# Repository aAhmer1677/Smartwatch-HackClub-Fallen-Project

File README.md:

# Smartwatch // HackClub Fallen Project

An open-source smartwatch built from scratch for the Hack Club Fallen. It runs on bare-metal ESP32-S3 with [[additional functions to be added]]

## The Backstory
Smartwatches have potential: You can strap them to your wrist and wear them everywhere. 

This smartwatch could:
- **Launch a private gateway:** you and your friends can then play in class.
- **Allow WIFI Connection to Your Mobile:** useful for that day you forgot your phone (basically calling with no additional sim card).
- **and much more**

I wanted to build a project so that other devs around the world can build upon this watch, including cool and interesting features that I couldn't have come up with myself.

## Compilation & Development

### We will be using:
- **ESP-IDF** - to compile and flash the firmware to the ESP32-S3
- **Android Studio** - to build and flash the Smartwatch App to our Android device *Samsung Galaxy A37 5G in my case*
- **EEZ Studio** - to create and compile the UI in LVGL
- **VS Code** - as the IDE for our overall project

### 1. Flash the firmware to the custom PCB

**Set the target device as an ESP32-S3**
```powershell
idf.py set-target esp32s3
```

**Open the built in terminal menu to configure variables**
```powershell
idf.py menuconfig
```

**Firmware Compilation**
```powershell
idf.py build
```

**Firmware Flashing & Serial Monitoring**
```powershell
# Replace COM3 with your own port
idf.py -p COM3 flash monitor
```

## File Structure
[To be finalised]

```text
Smartwatch Project
├── .github/
├── 3d-models/
|   ├── Chasis/
|   ├── Desings/
|   ├── Strap/
|   └── to print/
├── Android App/
├── assets/
|   ├── plan/
|   └── README/
├── PCB and Schematics/
├── firmware/
|   ├── managed-components/
|   ├── ui/
|   ├── CMakeLists.txt
|   ├── idf_component.yml
|   └── sdkconfig
├── .env.example
├── .gitignore
├── BOM.csv
├── LICENSE
├── plan.md
└── README.md
```

---
## The Project Plan
[`plan.md`](plan.md)

## Images of Product
### 3D Designs

## To Print
- ☐ Smartwatch chasis backplate
- ☐ Smartwatch chasis body
- ☐ Smartwatch strap long black + white mold
- ☐ Smartwatch strap long black mold
- ☐ Smartwatch strap short black + white mold
- ☐ Smartwatch strap short black mold
- ☐ Smartwatch strap short pin
- ☑

---

Built by Abdullah Ahmer for **Hack Club Fallen**

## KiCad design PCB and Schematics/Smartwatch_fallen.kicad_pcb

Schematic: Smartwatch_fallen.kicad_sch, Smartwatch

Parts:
C1, C2, C3, C4, C5, C6, C8, C12, C17, C18, C19: 10uF; C_0805_2012Metric; LCSC C15850
C7, C13, C14, C15, C16, C20, C21, C22, C23, C24, C25: 100nF; C_0603_1608Metric; LCSC C14663
C9, C10: 22uF; C_0805_2012Metric; LCSC C45783
C11: 1uF; C_0603_1608Metric; LCSC C15849
C40: 10µF; C0805; MPN CL21A106KAYNNNE; LCSC C15850
D1, D2: SS14; SMA_L4.2-W2.6-LS5.0-RD_1; MPN SS14; LCSC C2480
D3: CHG; LED-SMD_L1.6-W0.8-R-RD; MPN KT-0603R; LCSC C2286
D4: PGOOD; LED0603-RD; MPN CT-1608UGC-P4; LCSC C52675989
FB1, FB2, FB3: BLM18PG121SN1D; L0603; MPN BLM18PG121SN1D; LCSC C14709
H1, H2, H3, H4: MountingHole; MountingHole_2.2mm_M2
H5, H6, H7, H8, H9: HalfHole; MountingHole_2.2mm_M2
J1, J7: TYPE-C-31-M-12; USB-C_SMD-TYPE-C-31-M-12_1; MPN TYPE-C-31-M-12; LCSC C165948
J2: WIRELESS_RX; HDR-TH_2P-P2.54-V-M; MPN PZ254V-11-02P; LCSC C492401
J3: BATTERY; CONN-TH_B2B-PH-K-S; MPN B2B-PH-K-S(LF)(SN); LCSC C131337
J4: HAPTIC_MOTOR; HDR-TH_2P-P2.54-V-M; MPN PZ254V-11-02P; LCSC C492401
J5: ENCODER; HDR-TH_5P-P2.54-V-M; MPN PZ254V-11-05P; LCSC C492404
J6: HDMI-001 19PCBTP; HDMI-SMD_19P-P0.50-H-F; MPN HDMI-001 19PCBTP; LCSC C138388
J8: BX-TYPE-A-MWT4P; USB-A-SMD_BX-TYPE-A-MWT4P; MPN BX-TYPE-A-MWT4P; LCSC C18077687
L1: 0.47uH; IND-SMD_L2.0-W1.6_MHCHL201610A-1R0M-Q8A; MPN WIP201610P-R47ML; LCSC C964105
Q1: AO3400A; SOT-23-3_L2.9-W1.3-P1.90-LS2.4-BR; MPN AO3400A; LCSC C20917
R1, R2: 5.1k; R_0603_1608Metric; LCSC C23186
R3, R8, R9: 330k; R_0603_1608Metric; LCSC C23137
R4, R19: 100k; R_0603_1608Metric; LCSC C25803
R5, R20, R21: 2.2k; R_0603_1608Metric; LCSC C4190
R6, R7, R24: 510R; R_0603_1608Metric; LCSC C23193
R10: 510k; R_0603_1608Metric; LCSC C23192
R11: 91k; R_0603_1608Metric; LCSC C23265
R12, R13, R16, R17: 10k; R_0603_1608Metric; LCSC C25804
R14, R15, R23: 4.7k; R_0603_1608Metric; LCSC C23162
R18, R22: 1k; R_0603_1608Metric; LCSC C21190
R30, R31: 0603WAF5101T5E; R0603; MPN 0603WAF5101T5E; LCSC C23186
RT1: 10k NTC; R_0603_1608Metric; LCSC C13564
SW1: BOOT; SW-SMD_L3.9-W3.0-P4.45; MPN TS-1088-AR02016; LCSC C720477
SW2: RESET; SW-SMD_L3.9-W3.0-P4.45; MPN TS-1088-AR02016; LCSC C720477
U1: ESP32-S3-WROOM-2-N32R16V; WIRELM-SMD_L25.5-W18.0-P1.27_ESP32-S3-WROOM-2-N32R16V; MPN ESP32-S3-WROOM-2-N32R16V; LCSC C42417293
U2: USBLC6-2SC6; SOT-23-6_L2.9-W1.6-P0.95-LS2.8-BL; MPN USBLC6-2SC6; LCSC C7519
U3: TPS2116DRLR; SOT-583-8_L2.1-W1.6-P0.50-LS1.6-BL; MPN TPS2116DRLR; LCSC C3235557
U4: BQ24230RGTR; VQFN-16_L3.0-W3.0-P0.50-TL-EP; MPN BQ24230RGTR; LCSC C524814
U5: TPS63802DLAR; VSON-10_L3.0-W2.0-P0.50-TL; MPN TPS63802DLAR; LCSC C2845237
U6: ICM-20948; QFN-24_L3.0-W3.0-P0.40-BL-EP; MPN ICM-20948; LCSC C726001
U7: TFP410PAP; HTQFP-64_L10.0-W10.0-P0.50-LS12.0-BL-EP5.0; MPN TFP410PAP; LCSC C1543847

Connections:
3V3_D: C17.1, C20.1, C21.1, C22.1, FB1.1, U7.1 (DVDD), U7.12 (DVDD), U7.33 (DVDD)
3V3_P: C19.1, C25.1, FB3.1, U7.18 (PVDD)
3V3_T: C18.1, C23.1, C24.1, FB2.1, U7.23 (TVDD), U7.29 (TVDD)
+3V3: C9.1, C10.1, C12.1, C13.1, C14.1, C15.1, FB1.2, FB2.2, FB3.2, J5.5, R10.1, R12.1, R13.1, R14.1, R15.1, R16.1, R17.1, R23.2, U1.2 (3V3), U5.6 (VOUT), U6.8 (VDDIO), U6.13 (VDD), U6.22 (nCS), U7.3 (VREF), U7.9 (EDGE/HTPLG), U7.10 (~PD), U7.15 (BSEL/SCL)
/BAT_SENS: C7.1, R8.2, R9.1, U1.39 (IO1)
/BOOT: R13.2, SW1.2, U1.27 (IO0)
/EN: C11.2, R12.2, SW2.2, U1.3 (EN)
/ENC_A: J5.1, R16.2, U1.38 (IO2)
/ENC_B: J5.2, R17.2, U1.15 (IO3)
/ENC_SW: J5.3, U1.26 (IO45)
/FB: R10.2, R11.1, U5.4 (FB)
/HAPTIC_G: R18.1, U1.16 (IO46)
/I2C_SCL: R14.2, U1.37 (TXD0), U6.23 (SCL/SCLK)
/I2C_SDA: R15.2, U1.36 (RXD0), U6.24 (SDA/SDI)
/IMU_INT: U1.35 (IO42), U6.12 (INT1)
/LCD_B0: U1.19 (IO11), U7.60 (DATA3)
/LCD_B1: U1.20 (IO12), U7.59 (DATA4)
/LCD_B2: U1.21 (IO13), U7.58 (DATA5), U7.63 (DATA0)
/LCD_B3: U1.22 (IO14), U7.55 (DATA6), U7.62 (DATA1)
/LCD_B4: U1.23 (IO21), U7.54 (DATA7), U7.61 (DATA2)
/LCD_DE: U1.34 (IO41), U7.2 (DE)
/LCD_G0: U1.9 (IO16), U7.51 (DATA10)
/LCD_G1: U1.10 (IO17), U7.50 (DATA11)
/LCD_G2: U1.11 (IO18), U7.47 (DATA12)
/LCD_G3: U1.12 (IO8), U7.46 (DATA13)
/LCD_G4: U1.17 (IO9), U7.45 (DATA14), U7.53 (DATA8)
/LCD_G5: U1.18 (IO10), U7.44 (DATA15), U7.52 (DATA9)
/LCD_HSYNC: U1.32 (IO39), U7.4 (HSYNC)
/LCD_PCLK: U1.31 (IO38), U7.57 (IDCK+)
/LCD_R0: U1.4 (IO4), U7.40 (DATA19)
/LCD_R1: U1.5 (IO5), U7.39 (DATA20)
/LCD_R2: U1.6 (IO6), U7.38 (DATA21), U7.43 (DATA16)
/LCD_R3: U1.7 (IO7), U7.37 (DATA22), U7.42 (DATA17)
/LCD_R4: U1.8 (IO15), U7.36 (DATA23), U7.41 (DATA18)
/LCD_VSYNC: U1.33 (IO40), U7.5 (VSYNC)
/MOTOR_N: D2.1 (K), J4.2, Q1.3 (D)
/TMDS_CLK+: J6.10 (TMDSClock+), U7.22 (TXC+)
/TMDS_CLK-: J6.12 (TMDSClock-), U7.21 (TXC-)
/TMDS_D0+: J6.7 (TMDSData0+), U7.25 (TX0+)
/TMDS_D0-: J6.9 (TMDSData0-), U7.24 (TX0-)
/TMDS_D1+: J6.4 (TMDSData1+), U7.28 (TX1+)
/TMDS_D1-: J6.6 (TMDSData1-), U7.27 (TX1-)
/TMDS_D2+: J6.1 (TMDSData2+), U7.31 (TX2+)
/TMDS_D2-: J6.3 (TMDSData2-), U7.30 (TX2-)
/USB_DN: J1.A7 (DN1), J1.B7 (DN2), U1.13 (IO19), U2.3, U2.4
/USB_DP: J1.A6 (DP1), J1.B6 (DP2), U1.14 (IO20), U2.1, U2.6
/g: Q1.1 (G), R18.2, R19.1
/pr: R3.2, R4.1, U3.4 (PR1)
GND: C1.2, C2.2, C3.2, C4.2, C5.2, C6.2, C7.2, C8.2, C9.2, C10.2, C11.1, C12.2, C13.2, C14.2, C15.2, C16.2, C17.2, C18.2, C19.2, C20.2, C21.2, C22.2, C23.2, C24.2, C25.2, C40.2, J1.1 (EH), J1.2 (EH), J1.3 (EH), J1.4 (EH), J1.A1B12 (GND), J1.B1A12 (GND), J2.2, J3.2, J5.4, J6.2 (TMDSData2Shield), J6.5 (TMDSData1Shield), J6.8 (TMDSData0Shield), J6.11 (TMDSClockShield), J6.17 (DDC/CECGround), J6.20, J6.21, J6.22, J6.23, J7.1 (EH), J7.2 (EH), J7.3 (EH), J7.4 (EH), J7.A1B12 (GND), J7.B1A12 (GND), J8.4 (GND), J8.5, J8.6, Q1.2 (S), R1.2, R2.2, R4.2, R5.2, R9.2, R11.2, R19.2, R22.2, R24.2, R30.2, R31.2, RT1.2, SW1.1, SW2.1, U1.1 (GND), U1.40 (GND), U1.41 (EPAD), U2.2, U3.1 (GND), U4.4 (~CE), U4.5 (EN2), U4.8 (VSS), U4.15 (TD), U4.17 (EP), U5.2 (MODE), U5.3 (AGND), U5.8 (GND), U6.9 (SDO/AD0), U6.11 (FSYNC), U6.18 (GND), U6.20 (RESV), U6.25 (EP), U7.6 (CTL3/A3/DK3), U7.7 (CTL2/A2/DK2), U7.8 (CTL1/A1/DK1), U7.13 (ISEL/~RST), U7.14 (DSEL/SDA), U7.16 (DGND), U7.17 (PGND), U7.20 (TGND), U7.26 (TGND), U7.32 (TGND), U7.34 (RESERVED), U7.35 (DKEN), U7.48 (DGND), U7.56 (IDCK-), U7.64 (DGND), U7.65 (EP)
HDMI_5V: D1.1 (K), J6.18 (+5VPower), R20.2, R21.2
LCD_VBUS: C40.1, J7.A4B9 (VBUS), J7.B4A9 (VBUS)
unnamed: D3.1 (A), R6.2
unnamed: D3.2 (K), U4.9 (~CHG)
unnamed: D4.2 (A), R7.2
unnamed: D4.1 (C), U4.7 (~PGOOD)
unnamed: J1.A5 (CC1), R1.1
unnamed: J1.B5 (CC2), R2.1
unnamed: J6.19 (HotPlugDetect), R22.1
unnamed: J6.15 (SCL), R21.1
unnamed: J6.16 (SDA), R20.1
unnamed: R5.1, U4.16 (ISET)
unnamed: RT1.1, U4.1 (TS)
unnamed: L1.1, U5.9 (L1)
unnamed: L1.2, U5.7 (L2)
unnamed: C16.1, U6.10 (REGOUT)
unnamed: R23.1, U7.11 (MSEN/PO1)
unnamed: R24.1, U7.19 (TFADJ)
TOUCH_DN: J8.2 (D-)
TOUCH_DP: J8.3 (D+)
TOUCH_VBUS: J8.1 (VCC)
USBC_CC1: J7.A5 (CC1), R30.1
USBC_CC2: J7.B5 (CC2), R31.1
USBC_UNUSED: J7.A6 (DP1), J7.A7 (DN1), J7.A8 (SBU1), J7.B6 (DP2), J7.B7 (DN2), J7.B8 (SBU2)
VBAT: C6.1, J3.1, R8.1, U4.2 (BAT), U4.3 (BAT)
VBUS: C1.1, J1.A4B9 (VBUS), J1.B4A9 (VBUS), R3.1, U2.5, U3.3 (VIN1), U3.5 (MODE)
VMUX: C3.1, C4.1, D1.2 (A), U3.2 (VOUT), U3.7 (VOUT), U4.13 (IN)
VSYS: C5.1, C8.1, D2.2 (A), J4.1, R6.1, R7.1, U4.6 (EN1), U4.10 (OUT), U4.11 (OUT), U5.1 (EN), U5.10 (VIN)
VWL: C2.1, J2.1, U3.6 (VIN2)

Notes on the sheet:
ESP32-S3 MODULE
TFP410 DVI TX + HDMI
BATTERY CHARGER (BQ24230)
Smartwatch_REGION:eyJpZCI6IjNhYTRiNjZiLWU4Y2EtNDZmMS05ODk1LWQ5OWI1YTMzOGJlZiIsIm5hbWUiOiJFU1AzMi1TMyBNT0RVTEUiLCJ4MSI6NTI4My4yMDAwMDAwMDAwMDEsInkxIjoyMDMuMjAwMDAwMDAwMDAwMDUsIngyIjo2NTUzLjIwMDAwMDAwMDAwMSwieTIiOjE0NDcuOCwiY29sb3IiOjQyODY3MDk5MzAsImRlc2NyaXB0aW9uIjpudWxsLCJjb21wb25lbnRJZHMiOlsiM2NjM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
IMU, ENCODER, HAPTIC
3V3 BUCK-BOOST (TPS63802)
Smartwatch_REGION:eyJpZCI6IjhhNzg1NWRkLTkwMDktNGI3Zi1iYzcxLTNjZDNlODdkNTIzMyIsIm5hbWUiOiJVU0ItQyBJTlBVVCArIFBPV0VSIE1VWCIsIngxIjoyMDMuMTk5OTk5OTk5OTk5OTMsInkxIjoyMDMuMTk5OTk5OTk5OTk5OTMsIngyIjoyMDMyLjAsInkyIjoxMjcwLjAsImNvbG9yIjo0MjkxMjk3MjgwLCJkZXNjcmlwdGlvbiI6bnVsbCwiY29tcG9uZW50SWRzIjpbIjg3MDgxY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
Smartwatch_REGION:eyJpZCI6Ijk4MDhjNjVjLTA4MGQtNDg4YS1hZjNhLTkwNzNkNWFjM2UxYyIsIm5hbWUiOiIzVjMgQlVDSy1CT09TVCAoVFBTNjM4MDIpIiwieDEiOjQwNjMuOTk5OTk5OTk5OTk5NSwieTEiOjIwMy4yMDAwMDAwMDAwMDAwNSwieDIiOjUxODEuNTk5OTk5OTk5OTk4NSwieTIiOjgzOC4yLCJjb2xvciI6NDI3ODIxMzMyMCwiZGVzY3JpcHRpb24iOm51bGwsImNvbXBvbmVud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
MECHANICAL
Smartwatch_REGION:eyJpZCI6ImE1Njc5OTQ0LThiYWItNDJkZS04ZTU2LTRlMmNjZDBjMTE3ZiIsIm5hbWUiOiJNRUNIQU5JQ0FMIiwieDEiOjQ4MjYuMCwieTEiOjE1NDkuNCwieDIiOjY0MDAuNzk5OTk5OTk5OTk5LCJ5MiI6MTg3OS42LCJjb2xvciI6NDI4NDExMTQ1MCwiZGVzY3JpcHRpb24iOm51bGwsImNvbXBvbmVudElkcyI6WyJmYzNlZjdhOS1hM2RiLTUxYjQtYjQ2My0xMTM3MDIzY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
Smartwatch_REGION:eyJpZCI6ImIwYWMyZGE1LTNjNGYtNDU1Yi1iZGFkLTliNzc5OTVkZGVjYiIsIm5hbWUiOiJURlA0MTAgRFZJIFRYICsgSERNSSIsIngxIjoyMTMzLjYwMDAwMDAwMDAwMDQsInkxIjoxNTQ5LjQsIngyIjo0NzI0LjQsInkyIjozMzUyLjc5OTk5OTk5OTk5OTcsImNvbG9yIjo0Mjc4MjE4MzcwLCJkZXNjcmlwdGlvbiI6bnVsbCwiY29tcG9uZW50SWRzIjpbImRmZDAxNTk0L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
Smartwatch_REGION:eyJpZCI6ImIzNmRmOWIxLTY2MGYtNGQzYi1hMGYwLTRlOWZlNzgxZWQxNyIsIm5hbWUiOiJCQVRURVJZIENIQVJHRVIgKEJRMjQyMzApIiwieDEiOjIxMzMuNjAwMDAwMDAwMDAwNCwieTEiOjIwMy4xOTk5OTk5OTk5OTk5MywieDIiOjM5NjIuMzk5OTk5OTk5OTk5NiwieTIiOjEzNzEuNiwiY29sb3IiOjQyNzgyMjU5ODAsImRlc2NyaXB0aW9uIjpudWxsLCJjb21wb25lb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
USB-C INPUT + POWER MUX
Smartwatch_REGION:eyJpZCI6ImZhNDU4YTE0LWI0NDYtNDNjMC04YTYxLWVkNzc1NjQ1YmNhNSIsIm5hbWUiOiJJTVUsIEVOQ09ERVIsIEhBUFRJQyIsIngxIjoyMDMuMTk5OTk5OTk5OTk5OTMsInkxIjoxNTQ5LjM5OTk5OTk5OTk5OTksIngyIjoyMDMyLjAsInkyIjoyOTIxLjAsImNvbG9yIjo0MjkyNjM2MTYwLCJkZXNjcmlwdGlvbiI6bnVsbCwiY29tcG9uZW50SWRzIjpbIjg3MjE1N2FmL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

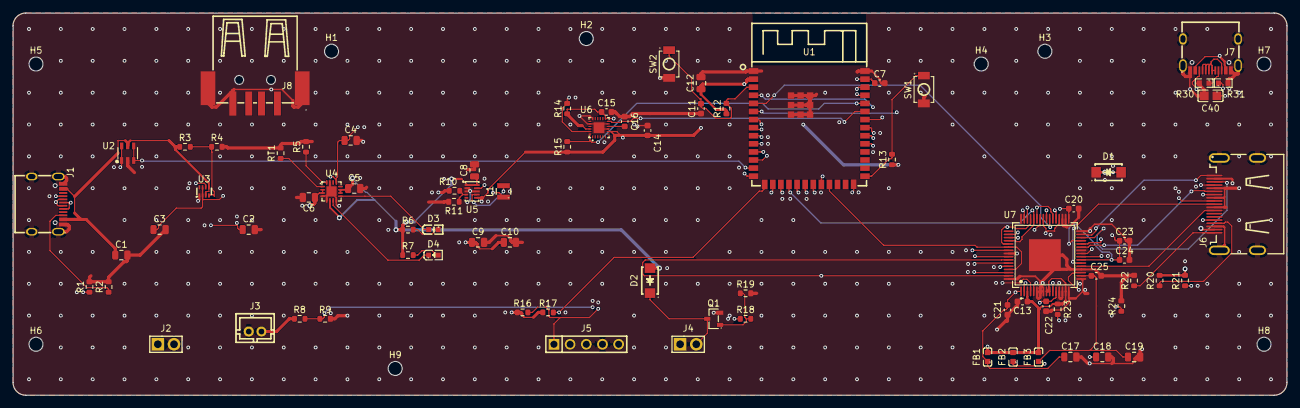
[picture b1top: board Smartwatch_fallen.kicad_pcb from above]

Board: 6 copper layers, 200.0 x 60.0 mm, 88 parts (0 on the bottom side), 75 nets.

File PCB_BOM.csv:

Id,Designator,Footprint,Quantity,Designation,Supplier and ref,Original Part,Matched Part Number,Quantity
1,"C1, C2, C3, C4, C5, C6, C8, C12, C17, C18, C19",C_0805_2012Metric,11,10uF,,10uF,CL21A106KAYNNNE,11
2,"C7, C13, C14, C15, C16, C20, C21, C22, C23, C24, C25",C_0603_1608Metric,11,100nF,,100nF,CL10B104KB8NNNC,11
3,"C9, C10",C_0805_2012Metric,2,22uF,,22uF,CL21A226MAQNNNE,2
4,C11,C_0603_1608Metric,1,1uF,,1uF,CL10A105KB8NNNC,1
5,C40,C0805,1,10µF,,10µF,CL21A106KAYNNNE,1
6,"D1, D2",SMA_L4.2-W2.6-LS5.0-RD_1,2,SS14,,SS14,SS14,2
7,D3,LED-SMD_L1.6-W0.8-R-RD,1,CHG,,CHG,KT-0603R,1
8,D4,LED0603-RD,1,PGOOD,,PGOOD,CT-1608UGC-P4,1
9,"FB1, FB2, FB3",L0603,3,BLM18PG121SN1D,,BLM18PG121SN1D,BLM18PG121SN1D,3
10,J1,USB-C_SMD-TYPE-C-31-M-12_1,1,TYPE-C-31-M-12,,TYPE-C-31-M-12,TYPE-C-31-M-12,1
11,J2,HDR-TH_2P-P2.54-V-M,1,WIRELESS_RX,,WIRELESS_RX,PZ254V-11-02P,1
12,J3,CONN-TH_B2B-PH-K-S,1,BATTERY,,BATTERY,B2B-PH-K-S(LF)(SN),1
13,J4,HDR-TH_2P-P2.54-V-M,1,HAPTIC_MOTOR,,HAPTIC_MOTOR,PZ254V-11-02P,1
14,J5,HDR-TH_5P-P2.54-V-M,1,ENCODER,,ENCODER,PZ254V-11-05P,1
15,J6,HDMI-SMD_19P-P0.50-H-F,1,HDMI-001 19PCBTP,,HDMI-001 19PCBTP,HDMI-001 19PCBTP,1
16,J7,USB-C_SMD-TYPE-C-31-M-12_1,1,TYPE-C-31-M-12,,TYPE-C-31-M-12,TYPE-C-31-M-12,1
17,J8,USB-A-SMD_BX-TYPE-A-MWT4P,1,BX-TYPE-A-MWT4P,,BX-TYPE-A-MWT4P,BX-TYPE-A-MWT4P,1
18,L1,IND-SMD_L2.0-W1.6_MHCHL201610A-1R0M-Q8A,1,0.47uH,,0.47uH,WIP201610P-R47ML,1
19,Q1,SOT-23-3_L2.9-W1.3-P1.90-LS2.4-BR,1,AO3400A,,AO3400A,AO3400A,1
20,"R1, R2",R_0603_1608Metric,2,5.1k,,5.1k,ERJ-3EKF5101V,2
21,"R3, R8, R9",R_0603_1608Metric,3,330k,,330k,ERJ-3EKF3303V,3
22,"R4, R19",R_0603_1608Metric,2,100k,,100k,ERJ-3EKF1003V,2
23,"R5, R20, R21",R_0603_1608Metric,3,2.2k,,2.2k,ERJ-3EKF2201V,3
24,"R6, R7, R24",R_0603_1608Metric,3,510R,,510R,ERJ-3EKF5100V,3
25,R10,R_0603_1608Metric,1,510k,,510k,ERJ-3EKF5103V,1
26,R11,R_0603_1608Metric,1,91k,,91k,ERJ-3EKF9102V,1
27,"R12, R13, R16, R17",R_0603_1608Metric,4,10k,,10k,ERJ-3EKF1002V,4
28,"R14, R15, R23",R_0603_1608Metric,3,4.7k,,4.7k,ERJ-3EKF4701V,3
29,"R18, R22",R_0603_1608Metric,2,1k,,1k,ERJ-3EKF1001V,2
30,"R30, R31",R0603,2,0603WAF5101T5E,,0603WAF5101T5E,0603WAF5101T5E,2
31,RT1,R_0603_1608Metric,1,10k NTC,,10k NTC,NCP18XH103F03RB,1
32,SW1,SW-SMD_L3.9-W3.0-P4.45,1,BOOT,,BOOT,TS-1088-AR02016,1
33,SW2,SW-SMD_L3.9-W3.0-P4.45,1,RESET,,RESET,TS-1088-AR02016,1
34,U1,WIRELM-SMD_L25.5-W18.0-P1.27_ESP32-S3-WROOM-2-N32R16V,1,ESP32-S3-WROOM-2-N32R16V,,ESP32-S3-WROOM-2-N32R16V,ESP32-S3-WROOM-2-N32R16V,1
35,U2,SOT-23-6_L2.9-W1.6-P0.95-LS2.8-BL,1,USBLC6-2SC6,,USBLC6-2SC6,USBLC6-2SC6,1
36,U3,SOT-583-8_L2.1-W1.6-P0.50-LS1.6-BL,1,TPS2116DRLR,,TPS2116DRLR,TPS2116DRLR,1
37,U4,VQFN-16_L3.0-W3.0-P0.50-TL-EP,1,BQ24230RGTR,,BQ24230RGTR,BQ24230RGTR,1
38,U5,VSON-10_L3.0-W2.0-P0.50-TL,1,TPS63802DLAR,,TPS63802DLAR,TPS63802DLAR,1
39,U6,QFN-24_L3.0-W3.0-P0.40-BL-EP,1,ICM-20948,,ICM-20948,ICM-20948,1
40,U7,HTQFP-64_L10.0-W10.0-P0.50-LS12.0-BL-EP5.0,1,TFP410PAP,,TFP410PAP,TFP410PAP,1
